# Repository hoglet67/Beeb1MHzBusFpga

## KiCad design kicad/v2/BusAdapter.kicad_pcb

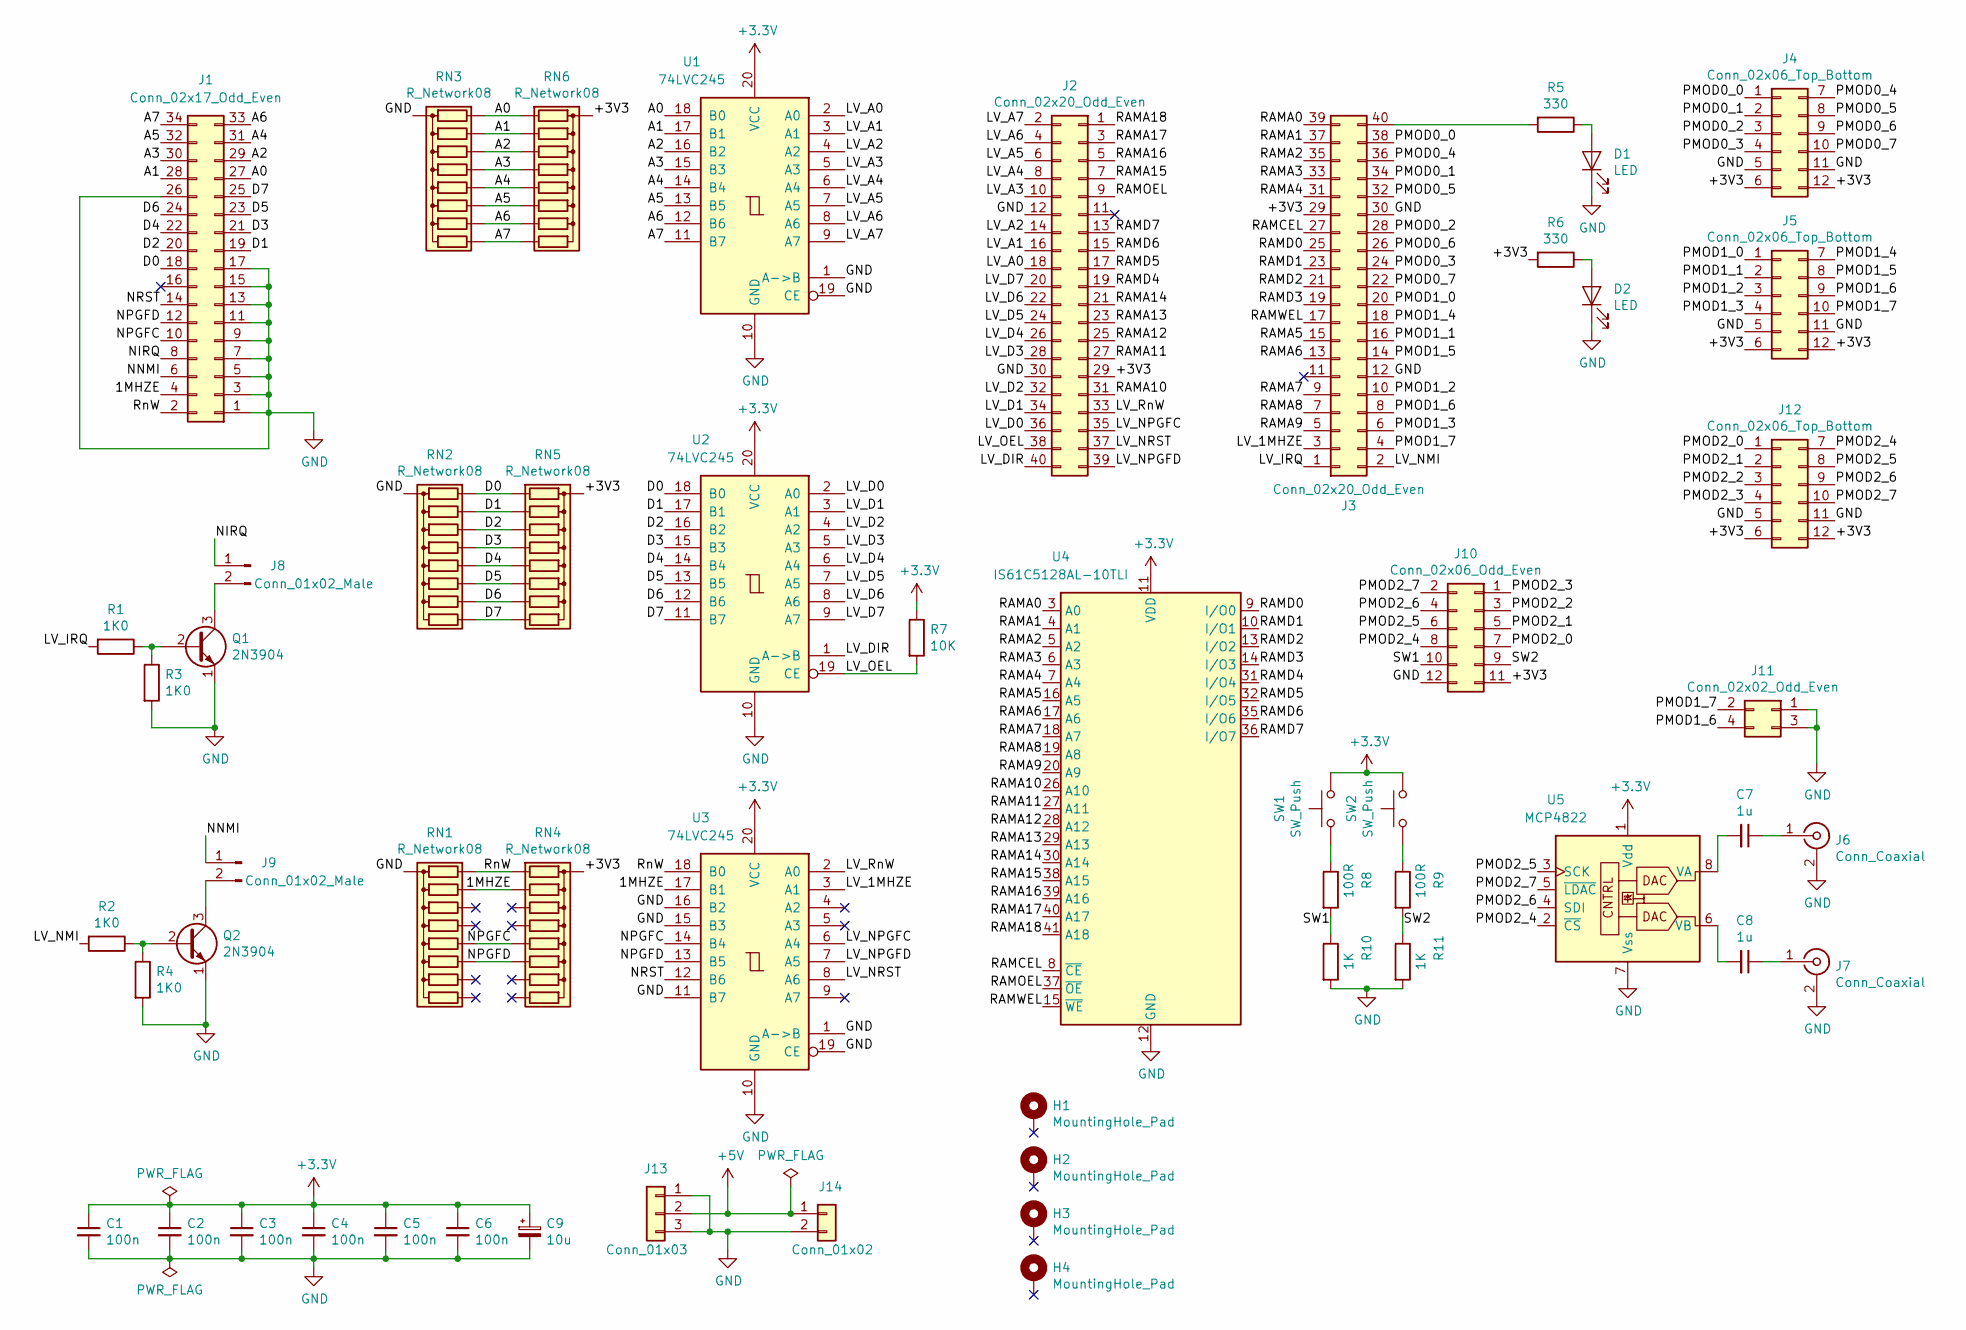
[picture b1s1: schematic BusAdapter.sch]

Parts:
C1, C2, C3, C4: 100n; C_Axial_L3.8mm_D2.6mm_P10.00mm_Horizontal
C5, C6: 100n; C_Axial_L3.8mm_D2.6mm_P7.50mm_Horizontal
C7, C8: 1u; C_Rect_L7.2mm_W5.5mm_P5.00mm_FKS2_FKP2_MKS2_MKP2
C9: 10u; CP_Radial_D5.0mm_P2.50mm
D1, D2: LED; LED_D3.0mm
H1, H2, H3, H4: MountingHole_Pad; MountingHole_3.2mm_M3_Pad
J1: Conn_02x17_Odd_Even; IDC-Header_2x17_P2.54mm_Horizontal_Lock
J2, J3: Conn_02x20_Odd_Even; PinSocket_2x20_P2.54mm_Vertical
J4, J5, J12: Conn_02x06_Top_Bottom; PinSocket_2x06_P2.54mm_Horizontal
J6, J7: Conn_Coaxial; phono
J8, J9: Conn_01x02_Male; PinHeader_1x02_P2.54mm_Vertical
J10: Conn_02x06_Odd_Even; PinSocket_2x06_P2.54mm_Vertical
J11: Conn_02x02_Odd_Even; PinHeader_2x02_P2.54mm_Vertical
J13: Conn_01x03; PinHeader_1x03_P2.54mm_Vertical
J14: Conn_01x02; PinSocket_1x02_P2.54mm_Vertical
Q1, Q2: 2N3904; TO-92_HandSolder
R1, R2, R3, R4: 1K0; R_Axial_DIN0207_L6.3mm_D2.5mm_P10.16mm_Horizontal
R5, R6: 330; R_Axial_DIN0207_L6.3mm_D2.5mm_P10.16mm_Horizontal
R7: 10K; R_Axial_DIN0207_L6.3mm_D2.5mm_P10.16mm_Horizontal
R8, R9: 100R; R_Axial_DIN0207_L6.3mm_D2.5mm_P10.16mm_Horizontal
R10, R11: 1K; R_Axial_DIN0207_L6.3mm_D2.5mm_P10.16mm_Horizontal
RN1, RN2, RN3, RN4, RN5, RN6: R_Network08; R_Array_SIP9
SW1, SW2: SW_Push; SW_PUSH_6mm_H5mm
U1, U2, U3: 74LVC245; DIP-20_W7.62mm_Socket
U4: IS61C5128AL-10TLI; TSOP-II-44_10.16x18.41mm_P0.8mm
U5: MCP4822; DIP-8_W7.62mm_Socket

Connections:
+5V: J13.2, J14.1
/1MHZE: J1.4, RN1.3 (R2), RN4.3 (R2), U3.17 (B1)
/A0: J1.27, RN3.2 (R1), RN6.2 (R1), U1.18 (B0)
/A1: J1.28, RN3.3 (R2), RN6.3 (R2), U1.17 (B1)
/A2: J1.29, RN3.4 (R3), RN6.4 (R3), U1.16 (B2)
/A3: J1.30, RN3.5 (R4), RN6.5 (R4), U1.15 (B3)
/A4: J1.31, RN3.6 (R5), RN6.6 (R5), U1.14 (B4)
/A5: J1.32, RN3.7 (R6), RN6.7 (R6), U1.13 (B5)
/A6: J1.33, RN3.8 (R7), RN6.8 (R7), U1.12 (B6)
/A7: J1.34, RN3.9 (R8), RN6.9 (R8), U1.11 (B7)
/D0: J1.18, RN2.2 (R1), RN5.2 (R1), U2.18 (B0)
/D1: J1.19, RN2.3 (R2), RN5.3 (R2), U2.17 (B1)
/D2: J1.20, RN2.4 (R3), RN5.4 (R3), U2.16 (B2)
/D3: J1.21, RN2.5 (R4), RN5.5 (R4), U2.15 (B3)
/D4: J1.22, RN2.6 (R5), RN5.6 (R5), U2.14 (B4)
/D5: J1.23, RN2.7 (R6), RN5.7 (R6), U2.13 (B5)
/D6: J1.24, RN2.8 (R7), RN5.8 (R7), U2.12 (B6)
/D7: J1.25, RN2.9 (R8), RN5.9 (R8), U2.11 (B7)
/LV_1MHZE: J3.3, U3.3 (A1)
/LV_A0: J2.18, U1.2 (A0)
/LV_A1: J2.16, U1.3 (A1)
/LV_A2: J2.14, U1.4 (A2)
/LV_A3: J2.10, U1.5 (A3)
/LV_A4: J2.8, U1.6 (A4)
/LV_A5: J2.6, U1.7 (A5)
/LV_A6: J2.4, U1.8 (A6)
/LV_A7: J2.2, U1.9 (A7)
/LV_D0: J2.36, U2.2 (A0)
/LV_D1: J2.34, U2.3 (A1)
/LV_D2: J2.32, U2.4 (A2)
/LV_D3: J2.28, U2.5 (A3)
/LV_D4: J2.26, U2.6 (A4)
/LV_D5: J2.24, U2.7 (A5)
/LV_D6: J2.22, U2.8 (A6)
/LV_D7: J2.20, U2.9 (A7)
/LV_DIR: J2.40, U2.1 (A->B)
/LV_IRQ: J3.1, R1.2
/LV_NMI: J3.2, R2.2
/LV_NPGFC: J2.35, U3.6 (A4)
/LV_NPGFD: J2.39, U3.7 (A5)
/LV_NRST: J2.37, U3.8 (A6)
/LV_OEL: J2.38, R7.2, U2.19 (CE)
/LV_RnW: J2.33, U3.2 (A0)
/NIRQ: J1.8, J8.1
/NNMI: J1.6, J9.1
/NPGFC: J1.10, RN1.6 (R5), RN4.6 (R5), U3.14 (B4)
/NPGFD: J1.12, RN1.7 (R6), RN4.7 (R6), U3.13 (B5)
/NRST: J1.14, U3.12 (B6)
/PMOD0_0: J3.38, J4.1
/PMOD0_1: J3.34, J4.2
/PMOD0_2: J3.28, J4.3
/PMOD0_3: J3.24, J4.4
/PMOD0_4: J3.36, J4.7
/PMOD0_5: J3.32, J4.8
/PMOD0_6: J3.26, J4.9
/PMOD0_7: J3.22, J4.10
/PMOD1_0: J3.20, J5.1
/PMOD1_1: J3.16, J5.2
/PMOD1_2: J3.10, J5.3
/PMOD1_3: J3.6, J5.4
/PMOD1_4: J3.18, J5.7
/PMOD1_5: J3.14, J5.8
/PMOD1_6: J3.8, J5.9, J11.4
/PMOD1_7: J3.4, J5.10, J11.2
/PMOD2_0: J10.7, J12.1
/PMOD2_1: J10.5, J12.2
/PMOD2_2: J10.3, J12.3
/PMOD2_3: J10.1, J12.4
/PMOD2_4: J10.8, J12.7, U5.2 (~CS)
/PMOD2_5: J10.6, J12.8, U5.3 (SCK)
/PMOD2_6: J10.4, J12.9, U5.4 (SDI)
/PMOD2_7: J10.2, J12.10, U5.5 (~LDAC)
/RAMA0: J3.39, U4.3 (A0)
/RAMA1: J3.37, U4.4 (A1)
/RAMA2: J3.35, U4.5 (A2)
/RAMA3: J3.33, U4.6 (A3)
/RAMA4: J3.31, U4.7 (A4)
/RAMA5: J3.15, U4.16 (A5)
/RAMA6: J3.13, U4.17 (A6)
/RAMA7: J3.9, U4.18 (A7)
/RAMA8: J3.7, U4.19 (A8)
/RAMA9: J3.5, U4.20 (A9)
/RAMA10: J2.31, U4.26 (A10)
/RAMA11: J2.27, U4.27 (A11)
/RAMA12: J2.25, U4.28 (A12)
/RAMA13: J2.23, U4.29 (A13)
/RAMA14: J2.21, U4.30 (A14)
/RAMA15: J2.7, U4.38 (A15)
/RAMA16: J2.5, U4.39 (A16)
/RAMA17: J2.3, U4.40 (A17)
/RAMA18: J2.1, U4.41 (A18)
/RAMCEL: J3.27, U4.8 (~CE)
/RAMD0: J3.25, U4.9 (I/O0)
/RAMD1: J3.23, U4.10 (I/O1)
/RAMD2: J3.21, U4.13 (I/O2)
/RAMD3: J3.19, U4.14 (I/O3)
/RAMD4: J2.19, U4.31 (I/O4)
/RAMD5: J2.17, U4.32 (I/O5)
/RAMD6: J2.15, U4.35 (I/O6)
/RAMD7: J2.13, U4.36 (I/O7)
/RAMOEL: J2.9, U4.37 (~OE)
/RAMWEL: J3.17, U4.15 (~WE)
/RnW: J1.2, RN1.2 (R1), RN4.2 (R1), U3.18 (B0)
/SW1: J10.10, R8.2, R10.1
/SW2: J10.9, R9.2, R11.1
GND: C1.2, C2.2, C3.2, C4.2, C5.2, C6.2, C9.2, D1.1 (K), D2.1 (K), J1.1, J1.3, J1.5, J1.7, J1.9, J1.11, J1.13, J1.15, J1.17, J1.26, J2.12, J2.30, J3.12, J3.30, J4.5, J4.11, J5.5, J5.11, J6.2 (Ext), J7.2 (Ext), J10.12, J11.1, J11.3, J12.5, J12.11, J13.1, J13.3, J14.2, Q1.1 (E), Q2.1 (E), R3.2, R4.2, R10.2, R11.2, RN1.1 (common), RN2.1 (common), RN3.1 (common), U1.1 (A->B), U1.10 (GND), U1.19 (CE), U2.10 (GND), U3.1 (A->B), U3.10 (GND), U3.11 (B7), U3.15 (B3), U3.16 (B2), U3.19 (CE), U4.12 (GND), U4.34 (GND), U5.7 (Vss)
unnamed: C7.1, J6.1 (In)
unnamed: C7.2, U5.8 (VA)
unnamed: C8.1, J7.1 (In)
unnamed: C8.2, U5.6 (VB)
unnamed: D1.2 (A), R5.1
unnamed: D2.2 (A), R6.1
unnamed: J3.40, R5.2
unnamed: J8.2, Q1.3 (C)
unnamed: J9.2, Q2.3 (C)
unnamed: Q1.2 (B), R1.1, R3.1
unnamed: Q2.2 (B), R2.1, R4.1
unnamed: R8.1, SW1.1
unnamed: R9.1, SW2.1

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
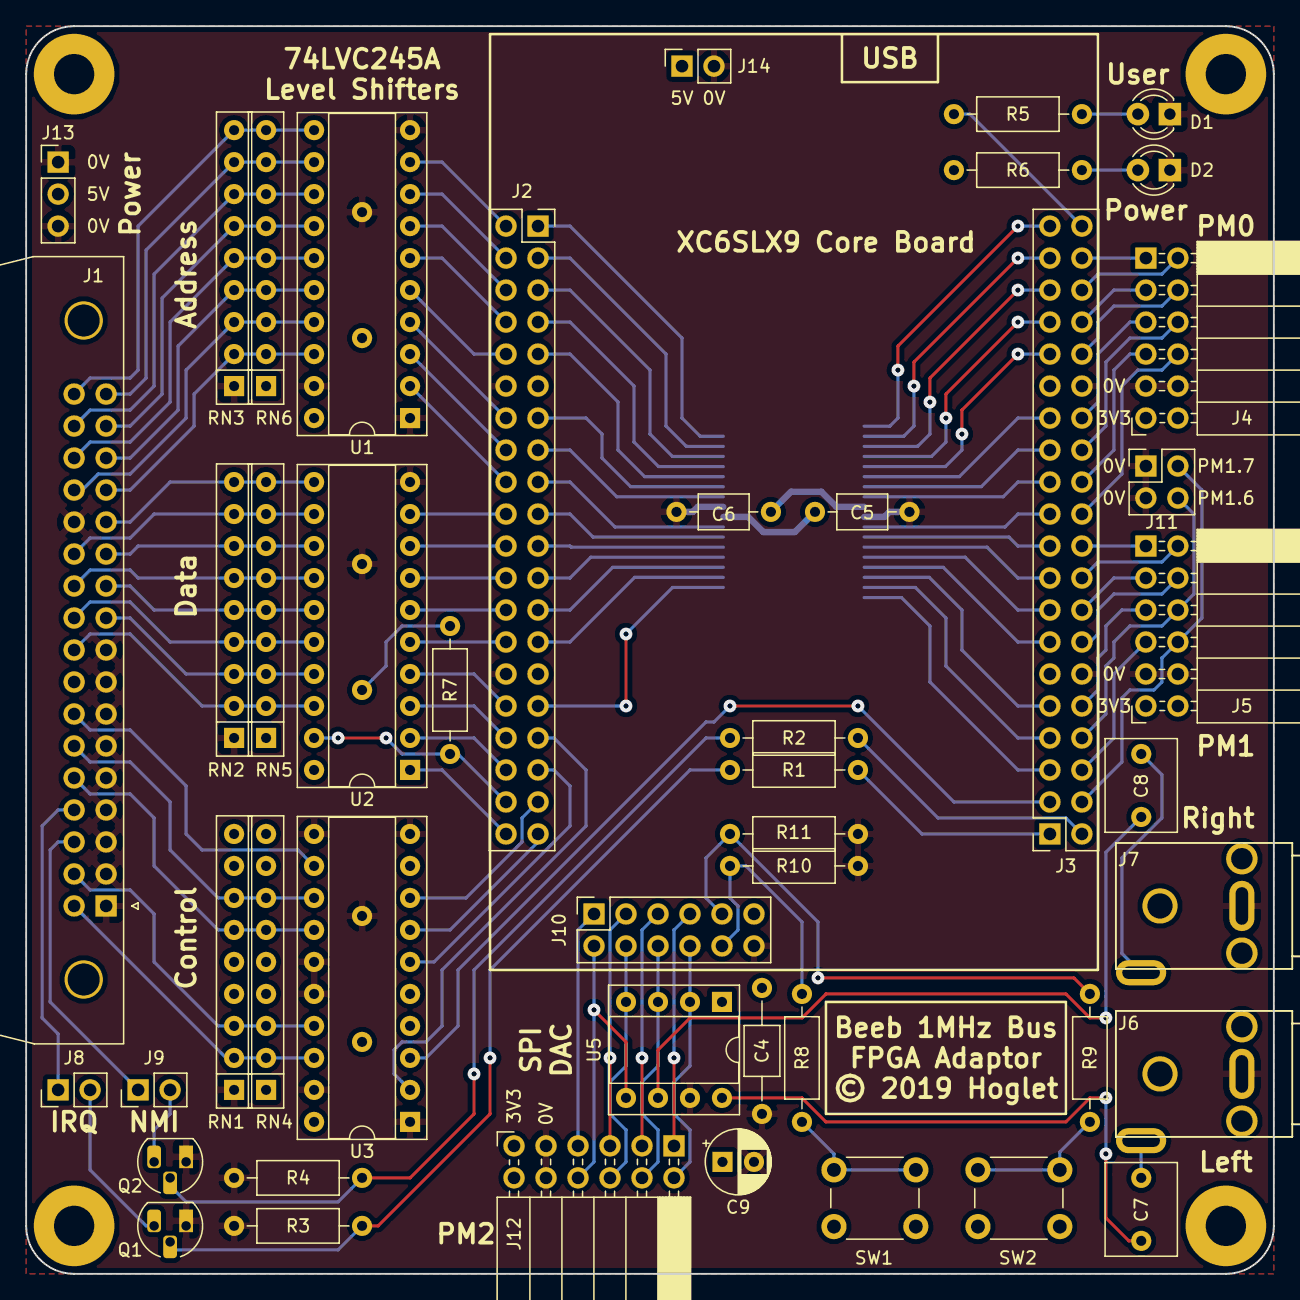
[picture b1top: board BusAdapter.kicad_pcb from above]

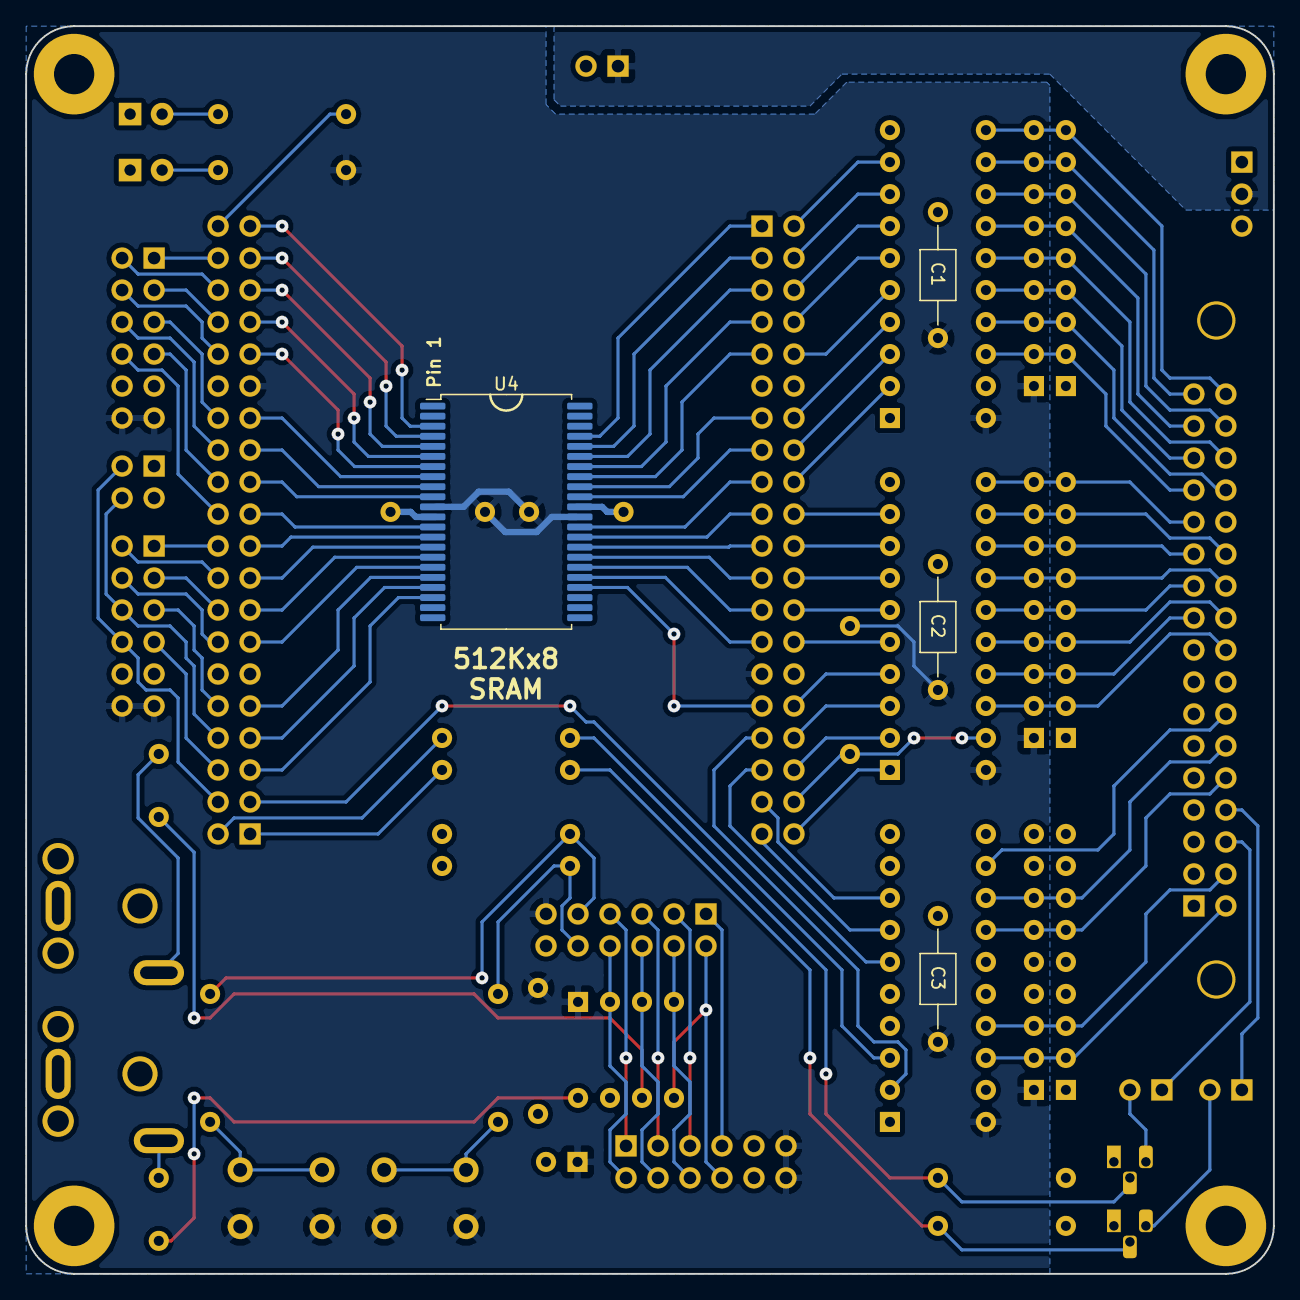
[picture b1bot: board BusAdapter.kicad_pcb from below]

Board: 2 copper layers, 99.1 x 99.1 mm, 55 parts (4 on the bottom side), 120 nets.

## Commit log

2019-03-01 Added v1 of 1MHz Bus FPGA Adapter PCB
2019-03-05 PCB: Added switches
2019-03-05 PCB: Added manufacturing data
2019-03-07 Added .gitignore
2019-03-07 PCB: Renamed project from Music5000 to BusAdapter
2019-03-07 Added Owl Logo source/binary
2019-04-01 PCB v2: Initial check-in
2019-04-01 PCB v2: Added pmod2 and updated layout
2019-04-01 PCB v2: Updated SW1/2 to HSWAPEN pulled low on power up
2019-04-01 PCB v2: Improved SRAM decoupling
2019-04-01 PCB v2: Improved SRAM decoupling even more
2019-04-02 PCB v2: Enlarged IDC connector holes; added power connector
2019-04-02 PCB v2: Made TSOP-II pads 0.5mm longer on the outside
2019-04-13 PCB v2: Refreshed design in KiCad 5.0.2-stable
2019-04-13 PCB v2: Solder Mask Clearance/Width = 0.15mm/0.40mm
2019-04-13 PCB v2: Added manufacturing files
2019-04-13 PCB v2: Corrected error with orientation of power connector
2019-04-13 PCB v2: Updated manufacturing files
2019-05-01 Added Creative Commons BY-NC-SA license
2019-05-03 Corrected SRAM part number on schematic
2019-05-03 Corrected RN and LED values on schematic
2019-06-10 Check in BBC Basic Loader
2019-06-10 Renamed fefd_test to owl
2019-06-10 Owl Logo: test for mode 7
2019-06-11 Owl Logo: test for soft break as early as possible
2020-02-12 Frame Buffer: initial commit
2020-03-29 Frame Buffer: added initial release
2020-04-07 Frame Buffer: .xise churn
2020-04-07 Frame Buffer: initial version of blitter
2020-04-07 Frame Buffer: added fill_op
2020-04-07 Frame Buffer: added char_op
2020-04-08 Frame Buffer: Also create .bin file
2020-04-08 Frame Buffer: added v2 release for Ed to test
2020-04-08 Frame Buffer: Simple OSWRCH implementation
2020-04-08 Frame Buffer: Optimize write-only ops (now 25M pixels/sec)
2020-04-08 Frame Buffer: use ODDR I/O fir driving external SRAM
2020-04-08 Frame Buffer: fix yellow tint (Ed was right!)
2020-04-09 Frame Buffer: work around a bug when scrolling
2020-04-09 Frame Buffer: Optimised OSWRCH character output
2020-04-09 Frame Buffer: Changed OSWRCH to use cursor_x,cursor_y
2020-04-09 Frame Buffer: Copy now: D = (S and mask) | (D and not mask)
2020-04-10 Frame Buffer: Added Palette
2020-04-10 Frame Buffer: Prisma 3 256-col RLE Image Reader
2020-04-10 Frame Buffer: Prisma 3 reader improvements
2020-04-10 Frame Buffer: Play nicely with other devices sharing the 1MHz Bus
2020-05-14 Life: initial checkin, just generates 1920x1080@60.6 video
2020-05-14 Life: some life-like activity!
2020-05-14 Life: simplify RAM Rd/Wr Addr generation (should wrap like a torus)
2020-05-14 Life: Added 1MHz Bus Interface
2020-05-14 Added 269.ssd
2020-05-14 Life: vhdl -> verilog
2020-05-14 Life: Delete vhdl version
2020-05-14 Life: Add 1600x1200 timings
2020-05-15 Life: Correct pipelining of video control signals
2020-05-15 Life: Mask writing close to the edges
2020-05-15 Life: make masking/wrapping controllable via bit 6 of ctrl reg
2020-05-15 Life: fix a bug with masking
2020-05-15 Life: support readback of frame buffer, and fix all warnings
2020-05-15 Life: change running only at start of frame
2020-05-15 Life: Add RLE Loader
2020-05-15 Life: Add in a Menu
2020-05-15 Life: Add packaging of release
2020-05-16 Life: Index RLE files on Disc
2020-05-16 Life: indexer now shows pattern size in menu
2020-05-16 Life: some new patterns
2020-05-16 Life: change border col to indicate edge mode
2020-05-16 Life: fix bug in name parsing
2020-05-16 Life: space toggles edge mode
2020-05-16 Life: Switch menu to MODE 0; add author
2020-05-17 Life: Add regs at &FCA1/2 for X/Y size in units of 8 pixels
2020-05-17 Life: App now determines screen size by reading hardware registers
2020-05-17 Life: reduce zero page usage
2020-05-17 Life: Support drive selection
2020-05-17 Life: optimise RLE reader, but bottleneck is in DFS/MMFS OSGBPB
2020-05-17 Life: use OSWORD 7F for reading RLE files
2020-05-17 Life: Comments
2020-05-17 Life: whitespace
2020-05-17 Add FPGA build script
2020-05-17 Life: rename patterns to patterns0
2020-05-17 Life: Pattern updates suggestions from Ed
2020-05-18 Life: build.sh now creates 4 disc images
2020-05-18 Life: hardware supports fast clear
2020-05-19 Life: Added single step (tab)
2020-05-19 Life: pipeline now 2 pixels wide, using DDR2 output registers
2020-05-19 Life: scaler (work in progress)
2020-05-20 Life: fix left edge scaler anomaly
2020-05-20 Life: scaler correctly wraps across edges (thanks Ed)
2020-05-20 Life: added hardware pan velocity registers
2020-05-20 Life: added fractional velocities
2020-05-20 Life: fix F0 for edge mode toggle
2020-05-20 Life: reorganize scaler write pipeline to eliminate discontinuity
2020-05-20 Life: minor discontinuity fix when pixel-pair straddles boundary
2020-05-20 Life: fudge 2 cell alignement issue
2020-05-21 Life: double buffer where zoom level allows it (memory constraint)
2020-05-21 Life: F5 toggles border visiblity in scaled view
2020-05-22 Life: add simulation files
2020-05-22 Life: initialize all regs to zero for the simulation
2020-05-22 Life: Really fix boundary condition bug (doh!)
2020-05-22 Life: load patterns at current origin, fix wrapping bugs
2020-05-22 Life: stop/start only after final write to playfield
2020-05-22 Life: Replace Queen Beeb with Glider (for testing)
2020-05-22 Life: Reverse the controls
2020-05-22 Life: fix issue where single step sometimes stepped twice
2020-05-22 Life: run clear_screen for two frames, to make sure the shift regs are flushed
2020-05-23 Life: pipeline now 8 pixels wide, extra row/col accesses to make a torus
2020-05-24 Life: add double buffering (plus slight rework of timing)
2020-05-24 Life: add ASIZE param
2020-05-24 Life: scaler: fix stepping in overlaid boundaries
2020-05-25 Life: updated simulation (writes FF to RAM)
2020-05-25 Life: fix broken 'Not Found' error
2020-05-25 Life: correctly wrap both X and Y coordinates when loading
2020-05-25 Life: update scaler to wrap lines correctly (almost)
2020-05-26 Life: simulation changes only
2020-05-26 Life: fix scaler issue around the l/r boundary at odd pixel offsets
2020-05-26 Life: fix issue when scaler windows wraps by exactly 1px
2020-05-26 Build: add the .bin file
2020-05-26 Life: experimental hacked 4x build
2020-05-27 Life: Cleaner implementation of (upto) 8 stage pipeline
2020-05-27 Life: , and . vary speed between 1x and 8x
2020-05-27 Life: fix bondary discontinuity at speeds > 1x
2020-05-27 Life: Add generation and cells counters
2020-05-27 Life: Add a status bar to the app
2020-05-27 Life: minor cursor positioning error
2020-05-28 Life: move registers to a special page in &FDxx
2020-05-28 Life: implement FPGA version checking
2020-05-28 Life: Read max speed from register
2020-05-28 Life: Increase the pipeline to 10 stages
2020-05-28 Life: updates to the status bar
2020-05-28 Life: Allow for two DCMs to be chained
2020-05-28 Life: fix a bug with panning introduced by the register changes
2020-05-28 Life: added 1024x768 and 1280x1024 params
2020-05-28 Life: make counter display more efficient (now takes ~7ms)
2020-05-28 Life: comments only
2020-05-29 Life: move scaler to a seperate module with it's own video clock
2020-05-29 Life: add promgen step to generate .mcs file (needs promgen on the path)
2020-05-30 Life: show resolution n title bar
2020-05-30 Life: Add multi-boot support
2020-05-30 Life: reduce 1920x1080 to 6 stages
2020-05-31 Life: implement partial double buffering of life playfield
2020-05-31 Life: add 1920x1200, update 1280x768, correct sync polarity
2020-06-01 Life: fix a scaler wrapping bug at 1920 wide
2020-06-01 Life: trucate height of x2 zoom window if necessary to fit in BRAM
2020-06-01 Life: fix origin issue at max speed by preloading one more line
2020-06-01 Life: add .bin format of multiboot for Pi based programmer
2020-06-02 Life: added Breeder 2
2020-06-02 Life: fix an indexer bug when switching disks
2020-06-02 Life: Make n_rst synchronous
2020-06-02 Life: Add Atom support
2020-06-03 Life: Atom: Build menu dynamically (using output of *CAT)
2020-06-03 Life: Atom: check for GODIL
2020-06-03 Life: tidy up build scripts
2020-06-03 Life: Add X/Y offsey to update_counts
2022-02-04 Added cyberbarter's Pi 4B guide

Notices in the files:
kicad/v2/BusAdapter.kicad_pcb:
© 2019 Hoglet
